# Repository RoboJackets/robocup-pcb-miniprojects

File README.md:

# Robocup 2026 Onboarding Project

## Description

This is the main repo for the 2026 onboarding season of Robojackets Robocup.

## Setup

Have ONE member of your team do this:

```sh
git clone https://github.com/RoboJackets/robocup-pcb-miniprojects
cd robocup-pcb-miniprojects
git checkout -b <your-team-name>
git push -u origin <your-team-name>
```

Now ALL members can:

```sh
git clone https://github.com/RoboJackets/robocup-pcb-miniprojects
cd robocup-pcb-miniprojects
git checkout <your-team-name>
```

This branch is where all work for your project should be done. Do not attempt to modify main, and especially do not try to modify other teams' branches.

## Overview

Your task is to create a daisy-chained sensor suite. Powered by the RP2040, this should be able to take a data packet from an SPI input, add to this packet, and pass it to the next board via SPI. Information for this packet is to be collected from the six distinct I2C devices on the board.

### PCB
Your KiCAD project folder and all other relevant files should be stored in [pcb](/pcb/).

See the [README](/pcb/README.md) for specific information.

### Firmware
Your Pico SDK project folder and all other relevant files should be stored in [firmware](/firmware/).

See the [README](/firmware/README.md) for specific information.

### Documentation

All live documentation (Hardware Reference Manuals, Technical Overviews, etc) should be stored in your team's drive folder which can be found [HERE](https://drive.google.com/drive/folders/1aSuq1g-BM3DlAOSG3E911sSWYeNv8i6k?usp=drive_link).

Start by copying the two template files from the project template folder [HERE](https://drive.google.com/drive/folders/1uaQHIUm1E482NEQLdI7As42oW3_wIS3i?usp=drive_link).

## Additional Notes

Project updates will be added here as needed

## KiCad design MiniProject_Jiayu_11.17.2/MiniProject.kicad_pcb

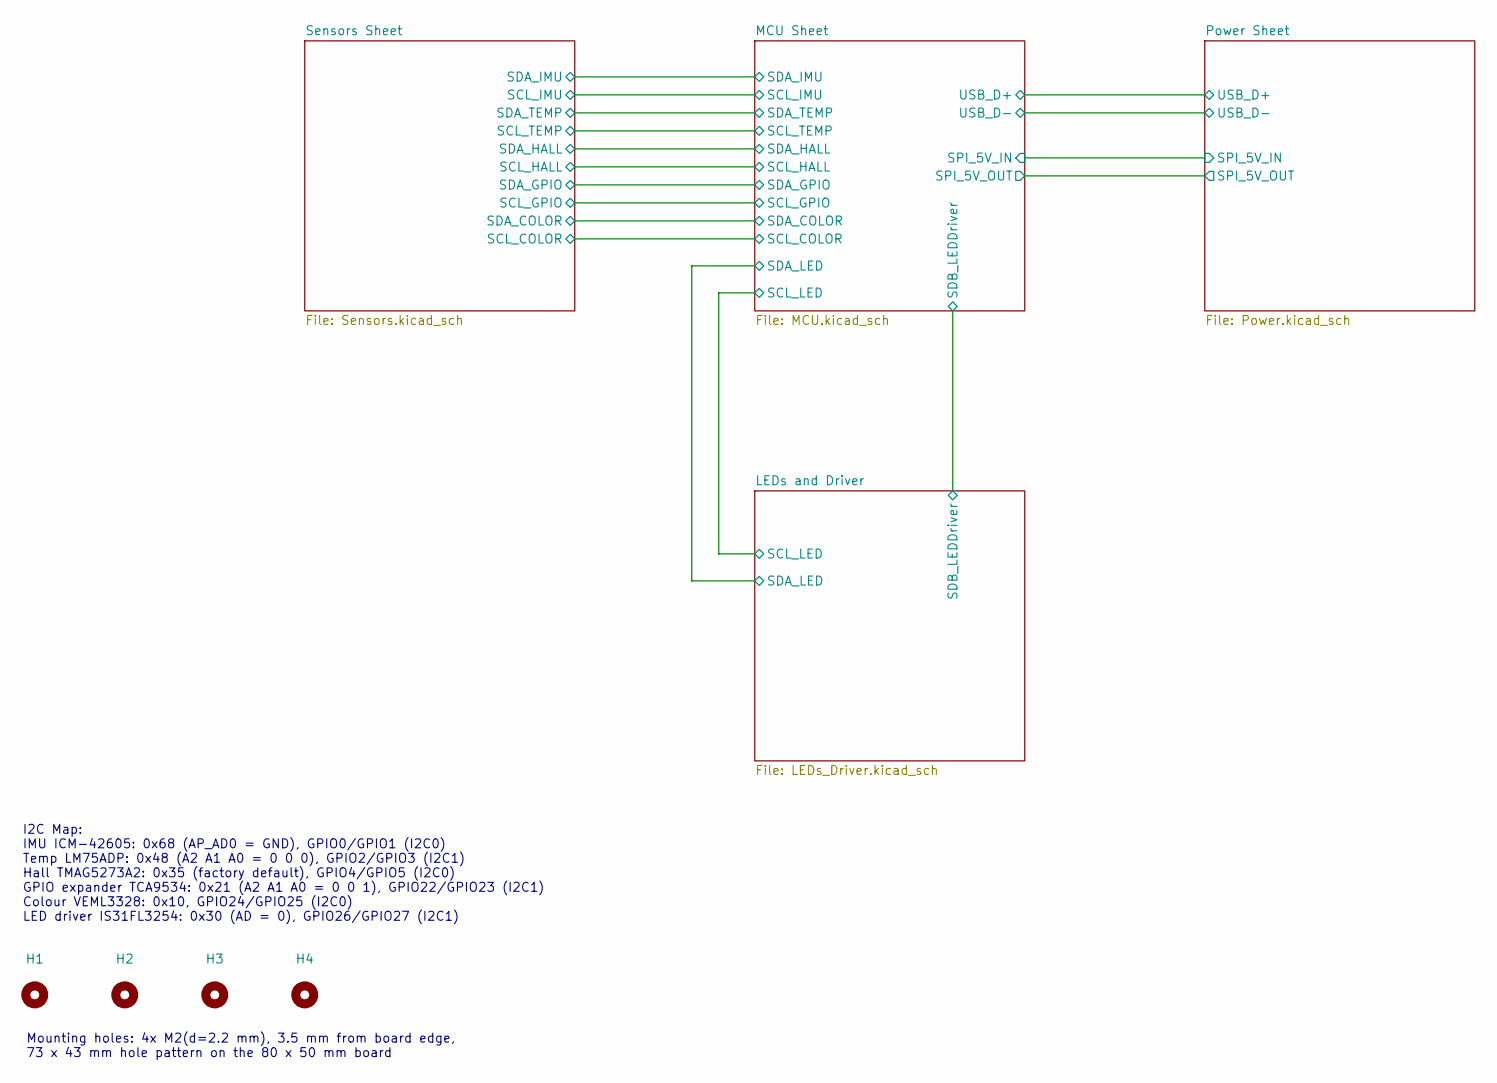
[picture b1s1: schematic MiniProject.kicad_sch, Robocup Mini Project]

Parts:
H1, H2, H3, H4: MountingHole; MountingHole_2.2mm_M2

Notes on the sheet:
I2C Map: IMU ICM-42605: 0x68 (AP_AD0 = GND), GPIO0/GPIO1 (I2C0) Temp LM75ADP: 0x48 (A2 A1 A0 = 0 0 0), GPIO2/GPIO3 (I2C1) Hall TMAG5273A2: 0x35 (factory default), GPIO4/GPIO5 (I2C0) GPIO expander TCA9534: 0x21 (A2 A1 A0 = 0 0 1), GPIO22/GPIO23 (I2C1) Colour VEML3328: 0x10, GPIO24/GPIO25 (I2C0) LED 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
Mounting holes: 4x M2(d=2.2 mm), 3.5 mm from board edge, 73 x 43 mm hole pattern on the 80 x 50 mm board

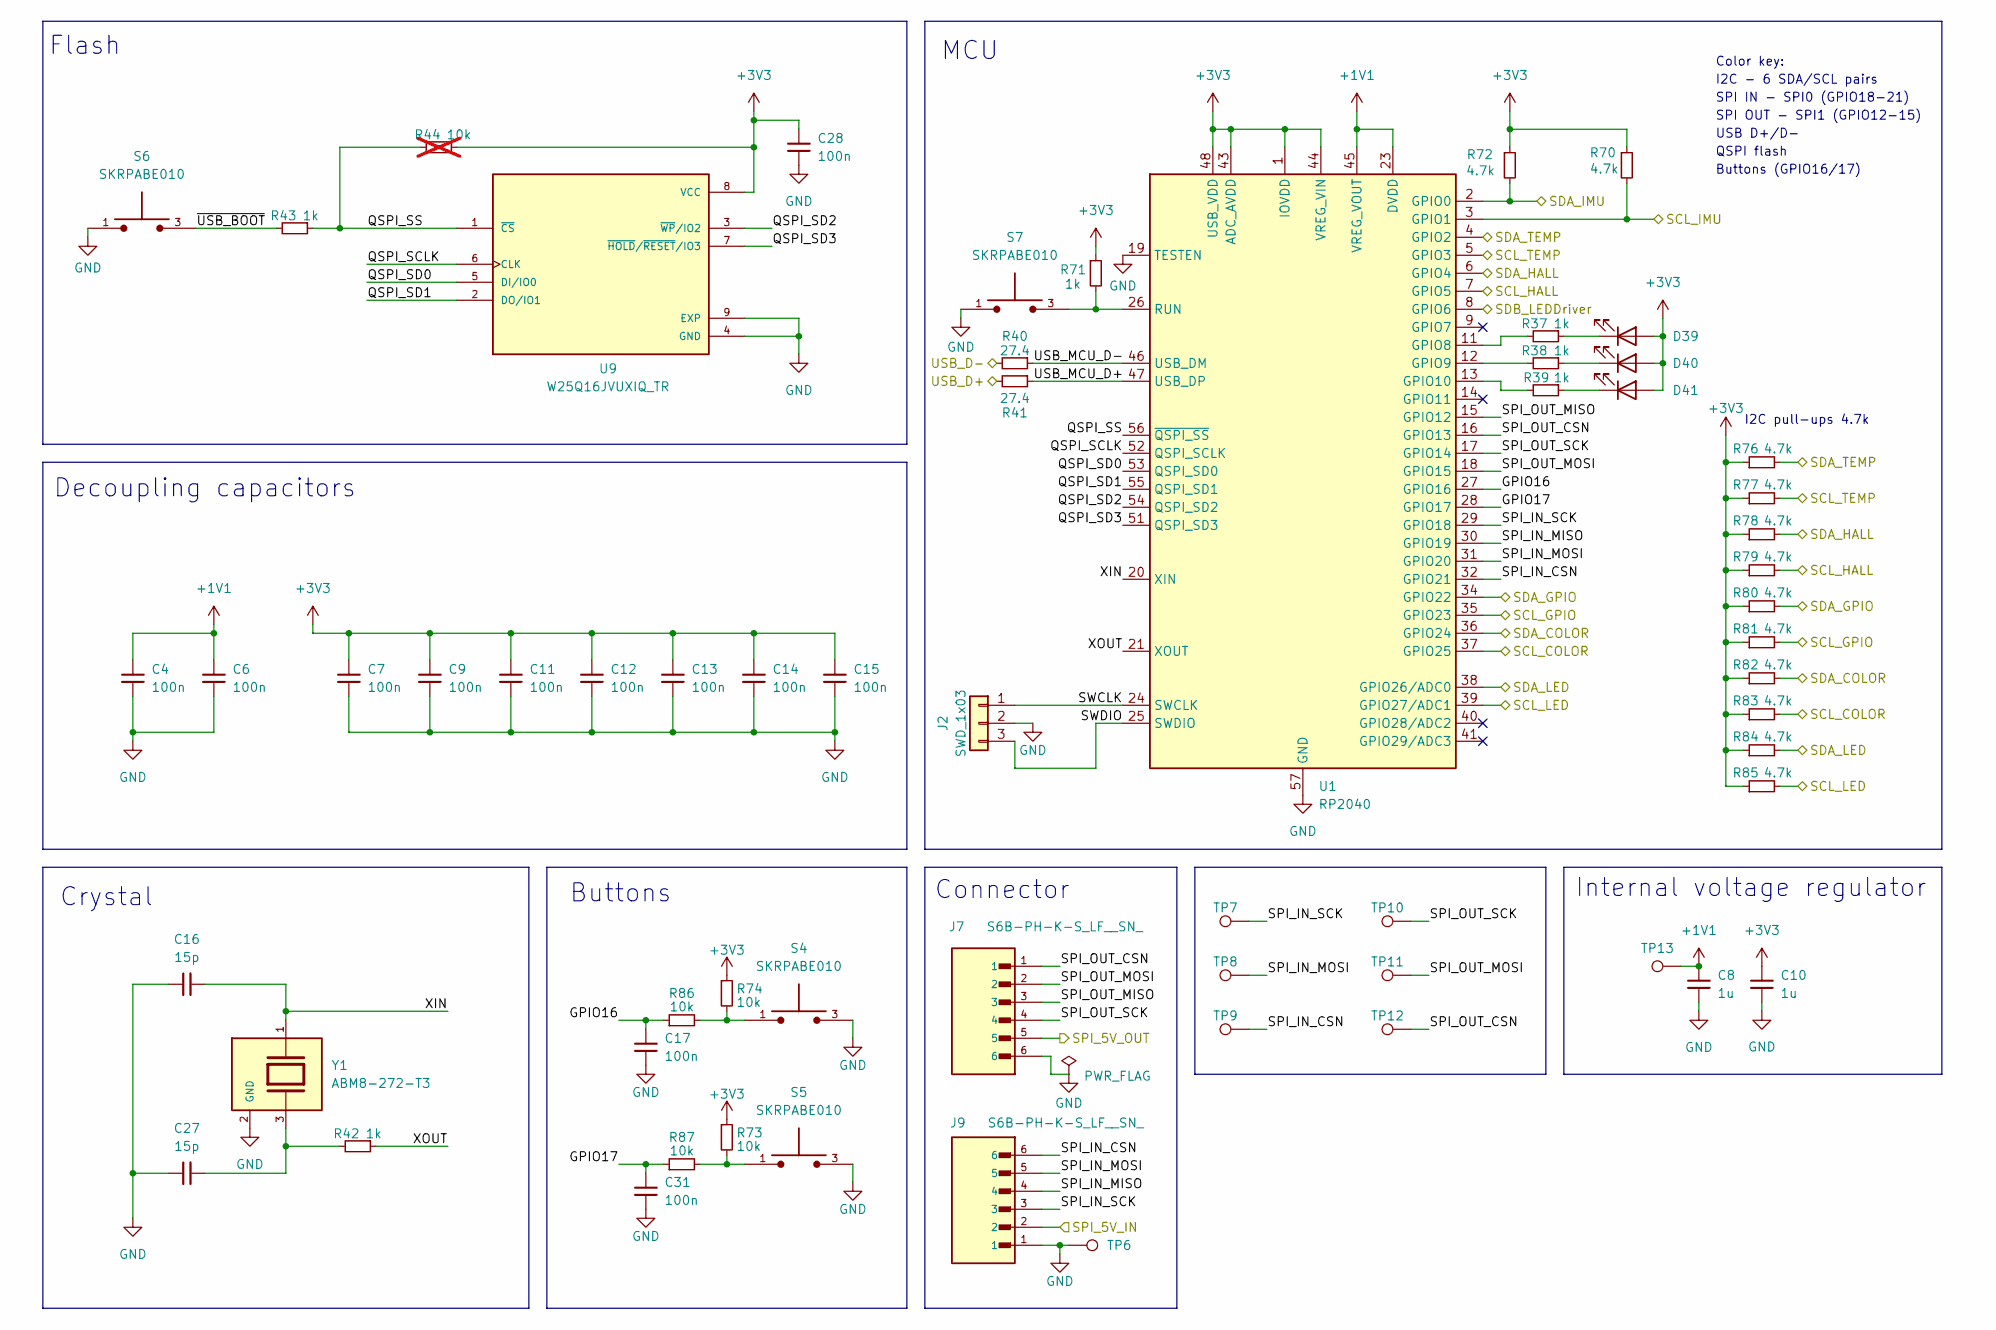
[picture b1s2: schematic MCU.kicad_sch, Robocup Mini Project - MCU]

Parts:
C4, C6, C7, C9, C11, C12, C13, C14, C15, C17, C28, C31: 100n; C_0402_1005Metric; Manufacturer P/N GRM155R71C104KA88J
C8, C10: 1u; C_0402_1005Metric; Manufacturer P/N CL05A105KA5NQNC
C16, C27: 15p; C_0402_1005Metric; Manufacturer P/N CL05C150JB5NNNC
D39, D40, D41: LED; LED_0603_1608Metric; Manufacturer P/N LTST-C191KGKT
J2: SWD_1x03; PinHeader_1x03_P2.54mm_Vertical; Manufacturer P/N TSW-103-07-G-S
J7, J9: S6B-PH-K-S_LF__SN_; JST_S6B-PH-K-S_LF__SN_; Manufacturer P/N S6B-PH-K-S
R37, R38, R39, R42, R43, R71: 1k; R_0402_1005Metric; Manufacturer P/N RC0402FR-071KL
R40, R41: 27.4; R_0402_1005Metric; Manufacturer P/N RC0402FR-0727R4L
R44: 10k; R_0402_1005Metric; Manufacturer P/N RC0402FR-0710KL; not fitted
R70, R72, R76, R77, R78, R79, R80, R81, R82, R83, R84, R85: 4.7k; R_0402_1005Metric; Manufacturer P/N RC0402FR-134K7L
R73, R74, R86, R87: 10k; R_0402_1005Metric; Manufacturer P/N RC0402FR-0710KL
S4, S5, S6, S7: SKRPABE010; SW_SKRPABE010; Manufacturer P/N SKRPABE010
TP6: GND; TestPoint_Pad_D1.0mm
TP7: SPI_IN_SCK; TestPoint_Pad_D1.0mm
TP8: SPI_IN_MOSI; TestPoint_Pad_D1.0mm
TP9: SPI_IN_CSN; TestPoint_Pad_D1.0mm
TP10: SPI_OUT_SCK; TestPoint_Pad_D1.0mm
TP11: SPI_OUT_MOSI; TestPoint_Pad_D1.0mm
TP12: SPI_OUT_CSN; TestPoint_Pad_D1.0mm
TP13: +1V1; TestPoint_Pad_D1.0mm
U1: RP2040; QFN-56-1EP_7x7mm_P0.4mm_EP3.2x3.2mm; Manufacturer P/N SC0914(13)
U9: W25Q16JVUXIQ_TR; Winbond_USON-8-1EP_3x2mm_P0.5mm_EP0.2x1.6mm; Manufacturer P/N W25Q16JVUXIQ TR
Y1: ABM8-272-T3; XTAL_ABM8-272-T3; Manufacturer P/N ABM8-272-T3

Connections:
+1V1: C4.1, C6.1, C8.1, TP13.1, U1.23 (DVDD), U1.45 (VREG_VOUT), U1.50 (DVDD)
+3V3: C7.1, C9.1, C10.1, C11.1, C12.1, C13.1, C14.1, C15.1, C28.1, D39.2 (A), D40.2 (A), D41.2 (A), R44.1, R70.1, R71.1, R72.1, R73.1, R74.1, R76.1, R77.1, R78.1, R79.1, R80.1, R81.1, R82.1, R83.1, R84.1, R85.1, U1.1 (IOVDD), U1.10 (IOVDD), U1.22 (IOVDD), U1.33 (IOVDD), U1.42 (IOVDD), U1.43 (ADC_AVDD), U1.44 (VREG_VIN), U1.48 (USB_VDD), U1.49 (IOVDD), U9.8 (VCC); also elsewhere on the board
/LEDs and Driver/SCL_LED: R85.2, U1.39 (GPIO27/ADC1); also elsewhere on the board
/LEDs and Driver/SDA_LED: R84.2, U1.38 (GPIO26/ADC0); also elsewhere on the board
/LEDs and Driver/SDB_LEDDriver: U1.8 (GPIO6); also elsewhere on the board
/MCU Sheet/GPIO16: C17.1, R86.1, U1.27 (GPIO16)
/MCU Sheet/GPIO17: C31.1, R87.1, U1.28 (GPIO17)
/MCU Sheet/QSPI_SCLK: U1.52 (QSPI_SCLK), U9.6 (CLK)
/MCU Sheet/QSPI_SD0: U1.53 (QSPI_SD0), U9.5 (DI/IO0)
/MCU Sheet/QSPI_SD1: U1.55 (QSPI_SD1), U9.2 (DO/IO1)
/MCU Sheet/QSPI_SD2: U1.54 (QSPI_SD2), U9.3 (~WP/IO2)
/MCU Sheet/QSPI_SD3: U1.51 (QSPI_SD3), U9.7 (~HOLD/~RESET/IO3)
/MCU Sheet/QSPI_SS: R43.1, R44.2, U1.56 (~QSPI_SS), U9.1 (~CS)
/MCU Sheet/SCL_COLOR: R83.2, U1.37 (GPIO25); also elsewhere on the board
/MCU Sheet/SCL_GPIO: R81.2, U1.35 (GPIO23); also elsewhere on the board
/MCU Sheet/SCL_HALL: R79.2, U1.7 (GPIO5); also elsewhere on the board
/MCU Sheet/SCL_IMU: R70.2, U1.3 (GPIO1); also elsewhere on the board
/MCU Sheet/SCL_TEMP: R77.2, U1.5 (GPIO3); also elsewhere on the board
/MCU Sheet/SDA_COLOR: R82.2, U1.36 (GPIO24); also elsewhere on the board
/MCU Sheet/SDA_GPIO: R80.2, U1.34 (GPIO22); also elsewhere on the board
/MCU Sheet/SDA_HALL: R78.2, U1.6 (GPIO4); also elsewhere on the board
/MCU Sheet/SDA_IMU: R72.2, U1.2 (GPIO0); also elsewhere on the board
/MCU Sheet/SDA_TEMP: R76.2, U1.4 (GPIO2); also elsewhere on the board
/MCU Sheet/SPI_5V_IN: J9.2; also elsewhere on the board
/MCU Sheet/SPI_5V_OUT: J7.5; also elsewhere on the board
/MCU Sheet/SPI_IN_CSN: J9.6, TP9.1 (1_1), U1.32 (GPIO21)
/MCU Sheet/SPI_IN_MISO: J9.4, U1.30 (GPIO19)
/MCU Sheet/SPI_IN_MOSI: J9.5, TP8.1 (1_1), U1.31 (GPIO20)
/MCU Sheet/SPI_IN_SCK: J9.3, TP7.1 (1_1), U1.29 (GPIO18)
/MCU Sheet/SPI_OUT_CSN: J7.1, TP12.1 (1_1), U1.16 (GPIO13)
/MCU Sheet/SPI_OUT_MISO: J7.3, U1.15 (GPIO12)
/MCU Sheet/SPI_OUT_MOSI: J7.2, TP11.1 (1_1), U1.18 (GPIO15)
/MCU Sheet/SPI_OUT_SCK: J7.4, TP10.1 (1_1), U1.17 (GPIO14)
/MCU Sheet/SWCLK: J2.1, U1.24 (SWCLK)
/MCU Sheet/SWDIO: J2.3, U1.25 (SWDIO)
/MCU Sheet/USB_D+: R41.2; also elsewhere on the board
/MCU Sheet/USB_D-: R40.2; also elsewhere on the board
/MCU Sheet/USB_MCU_D+: R41.1, U1.47 (USB_DP)
/MCU Sheet/USB_MCU_D-: R40.1, U1.46 (USB_DM)
/MCU Sheet/XIN: C16.2, U1.20 (XIN), Y1.1
/MCU Sheet/XOUT: R42.1, U1.21 (XOUT)
/MCU Sheet/~USB_BOOT: R43.2, S6.3, S6.4
GND: C4.2, C6.2, C7.2, C8.2, C9.2, C10.2, C11.2, C12.2, C13.2, C14.2, C15.2, C16.1, C17.2, C27.1, C28.2, C31.2, J2.2, J7.6, J9.1, S4.3, S4.4, S5.3, S5.4, S6.1, S6.2, S7.1, S7.2, TP6.1 (1_1), U1.19 (TESTEN), U1.57 (GND), U9.4 (GND), U9.9 (EXP), Y1.2 (GND), Y1.4 (GND); also elsewhere on the board
unnamed: C27.2, R42.2, Y1.3
unnamed: D39.1 (K), R37.1
unnamed: D40.1 (K), R38.1
unnamed: D41.1 (K), R39.1
unnamed: R73.2, R87.2, S5.1, S5.2
unnamed: R74.2, R86.2, S4.1, S4.2
unnamed: R37.2, U1.11 (GPIO8)
unnamed: R38.2, U1.12 (GPIO9)
unnamed: R39.2, U1.13 (GPIO10)
unnamed: R71.2, S7.3, S7.4, U1.26 (RUN)

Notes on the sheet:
SPI OUT - SPI1 (GPIO12-15)
I2C - 6 SDA/SCL pairs
Connector
SPI IN - SPI0 (GPIO18-21)
I2C pull-ups 4.7k
Decoupling capacitors
QSPI flash
Flash
Internal voltage regulator
Buttons
Color key:
USB D+/D-
Crystal
Buttons (GPIO16/17)
MCU

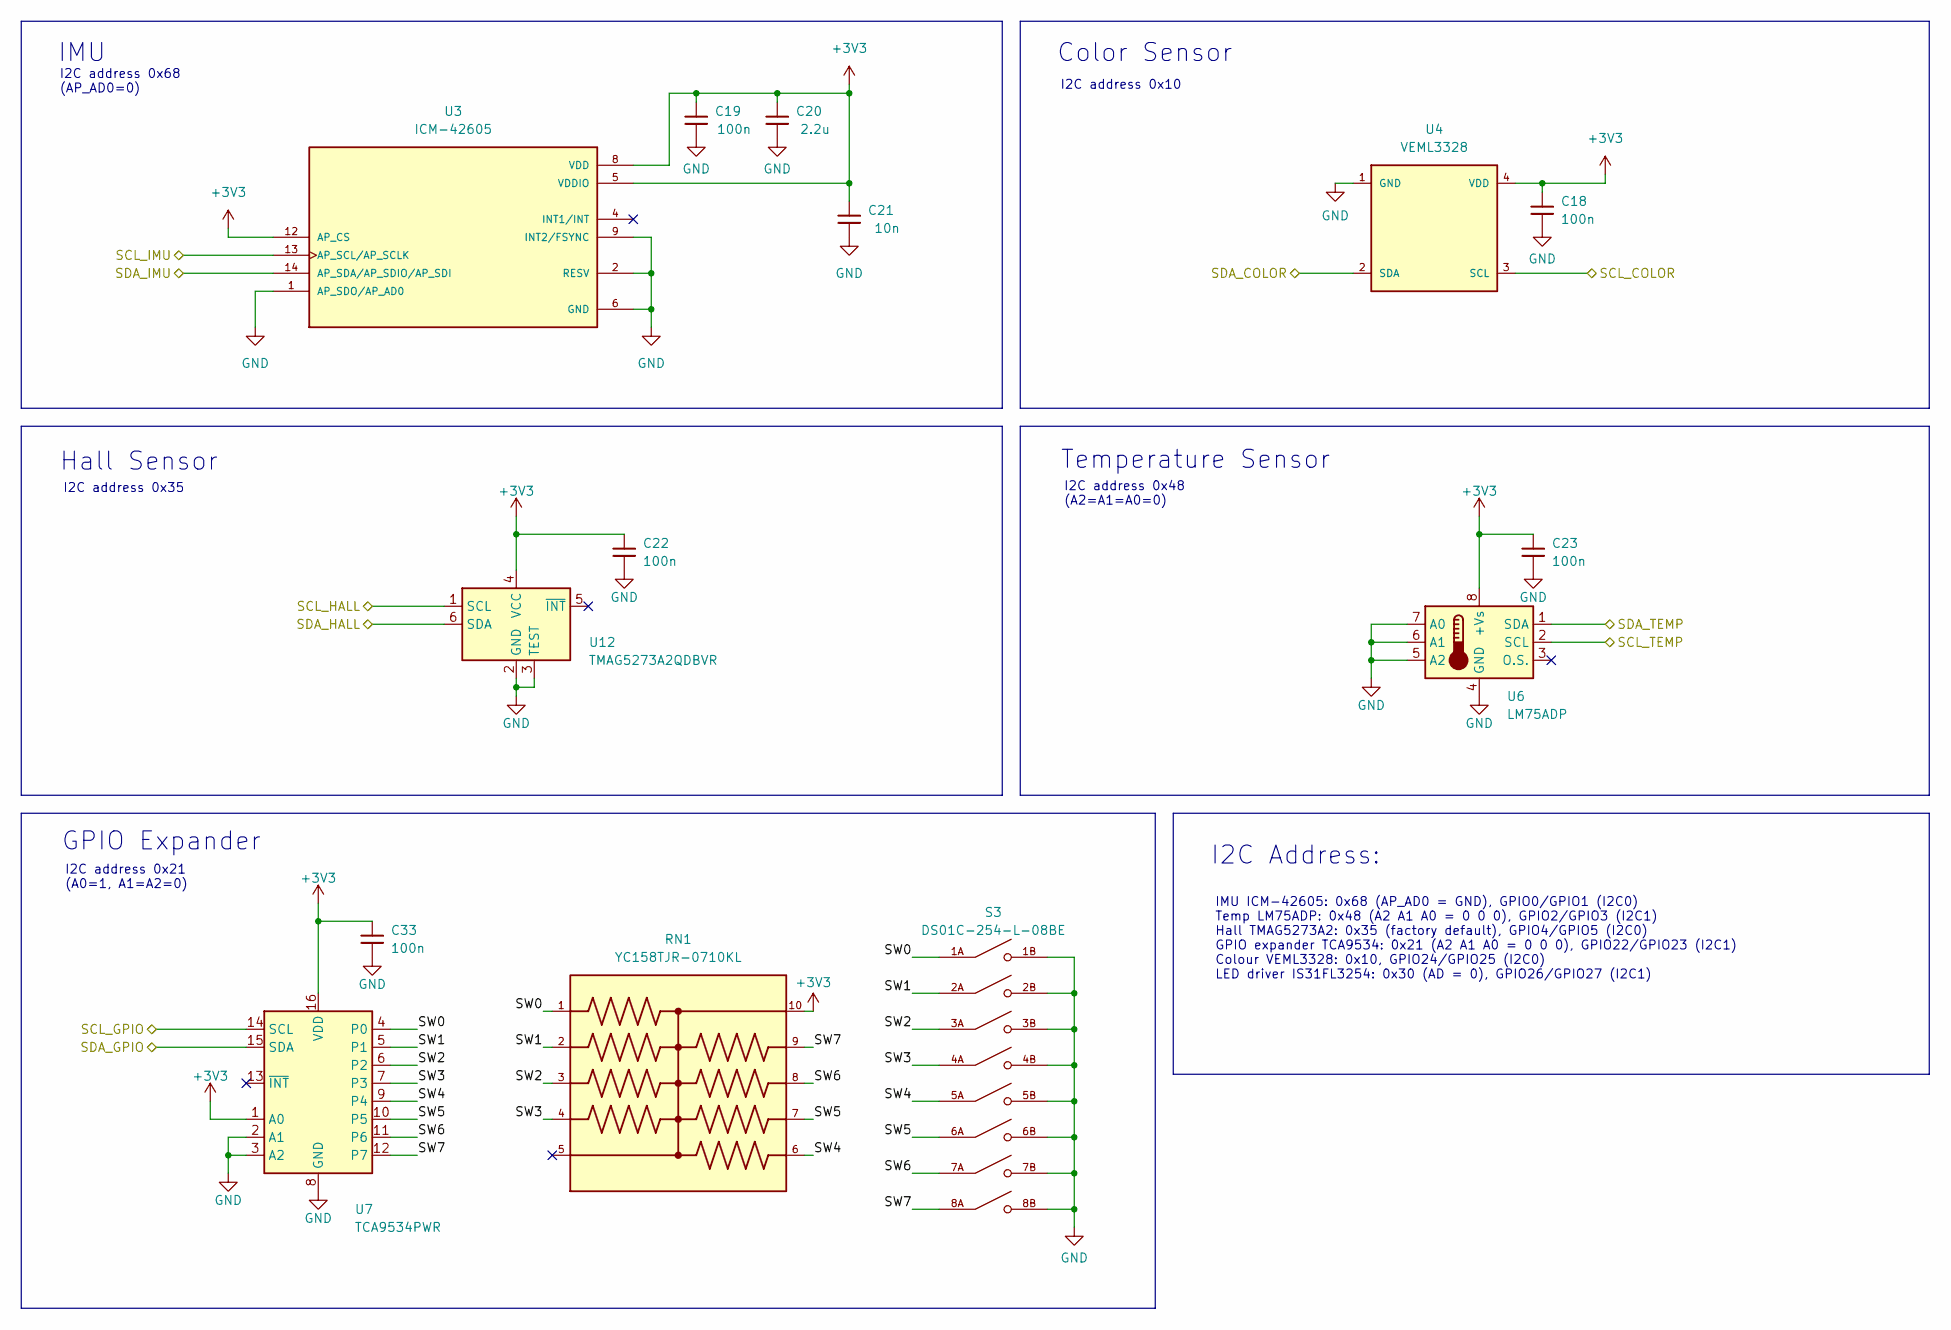
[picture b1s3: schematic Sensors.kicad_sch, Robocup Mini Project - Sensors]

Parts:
C18, C19, C22, C23, C33: 100n; C_0402_1005Metric; Manufacturer P/N GRM155R71C104KA88J
C20: 2.2u; C_0402_1005Metric; Manufacturer P/N LMK105BJ225KV-F
C21: 10n; C_0402_1005Metric; Manufacturer P/N CL05B103KB5NNNC
RN1: YC158TJR-0710KL; RESCAXE64P320X160X70-10N; Manufacturer P/N YC158TJR-0710KL
S3: DS01C-254-L-08BE; SW_DS01C-254-L-08BE; Manufacturer P/N DS01C-254-L-08BE
U3: ICM-42605; XDCR_ICM-42605; Manufacturer P/N ICM-42605
U4: VEML3328; Manufacturer P/N VEML3328
U6: LM75ADP; TSSOP-8_3x3mm_P0.65mm; Manufacturer P/N LM75ADP,118
U7: TCA9534PWR; SOP65P640X120-16N; Manufacturer P/N TCA9534PWR
U12: TMAG5273A2QDBVR; SOT95P280X140-6N; Manufacturer P/N TMAG5273A2QDBVR

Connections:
+3V3: C18.1, C19.1, C20.1, C21.1, C22.1, C23.1, C33.1, RN1.10, U3.5 (VDDIO), U3.8 (VDD), U3.12 (AP_CS), U4.4 (VDD), U6.8 (+Vs), U7.1 (A0), U7.16 (VCC), U12.4 (VCC); also elsewhere on the board
/MCU Sheet/SCL_COLOR: U4.3 (SCL); also elsewhere on the board
/MCU Sheet/SCL_GPIO: U7.14 (SCL); also elsewhere on the board
/MCU Sheet/SCL_HALL: U12.1 (SCL); also elsewhere on the board
/MCU Sheet/SCL_IMU: U3.13 (AP_SCL/AP_SCLK); also elsewhere on the board
/MCU Sheet/SCL_TEMP: U6.2 (SCL); also elsewhere on the board
/MCU Sheet/SDA_COLOR: U4.2 (SDA); also elsewhere on the board
/MCU Sheet/SDA_GPIO: U7.15 (SDA); also elsewhere on the board
/MCU Sheet/SDA_HALL: U12.6 (SDA); also elsewhere on the board
/MCU Sheet/SDA_IMU: U3.14 (AP_SDA/AP_SDIO/AP_SDI); also elsewhere on the board
/MCU Sheet/SDA_TEMP: U6.1 (SDA); also elsewhere on the board
/Sensors Sheet/SW0: RN1.1, S3.1A, U7.4 (P0)
/Sensors Sheet/SW1: RN1.2, S3.2A, U7.5 (P1)
/Sensors Sheet/SW2: RN1.3, S3.3A, U7.6 (P2)
/Sensors Sheet/SW3: RN1.4, S3.4A, U7.7 (P3)
/Sensors Sheet/SW4: RN1.6, S3.5A, U7.9 (P4)
/Sensors Sheet/SW5: RN1.7, S3.6A, U7.10 (P5)
/Sensors Sheet/SW6: RN1.8, S3.7A, U7.11 (P6)
/Sensors Sheet/SW7: RN1.9, S3.8A, U7.12 (P7)
GND: C18.2, C19.2, C20.2, C21.2, C22.2, C23.2, C33.2, S3.1B, S3.2B, S3.3B, S3.4B, S3.5B, S3.6B, S3.7B, S3.8B, U3.1 (AP_SDO/AP_AD0), U3.2 (RESV), U3.3 (RESV), U3.6 (GND), U3.7 (RESV), U3.9 (INT2/FSYNC), U3.10 (RESV), U3.11 (RESV), U4.1 (GND), U6.4 (GND), U6.5 (A2), U6.6 (A1), U6.7 (A0), U7.2 (A1), U7.3 (A2), U7.8 (GND), U12.2 (GND), U12.3 (TEST); also elsewhere on the board

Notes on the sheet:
Temperature Sensor
I2C Address:
IMU ICM-42605: 0x68 (AP_AD0 = GND), GPIO0/GPIO1 (I2C0) Temp LM75ADP: 0x48 (A2 A1 A0 = 0 0 0), GPIO2/GPIO3 (I2C1) Hall TMAG5273A2: 0x35 (factory default), GPIO4/GPIO5 (I2C0) GPIO expander TCA9534: 0x21 (A2 A1 A0 = 0 0 0), GPIO22/GPIO23 (I2C1) Colour VEML3328: 0x10, GPIO24/GPIO25 (I2C0) LED driver IS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
GPIO Expander
I2C address 0x21 (A0=1, A1=A2=0)
Color Sensor
I2C address 0x68 (AP_AD0=0)
I2C address 0x35
Hall Sensor
IMU
I2C address 0x10
I2C address 0x48 (A2=A1=A0=0)

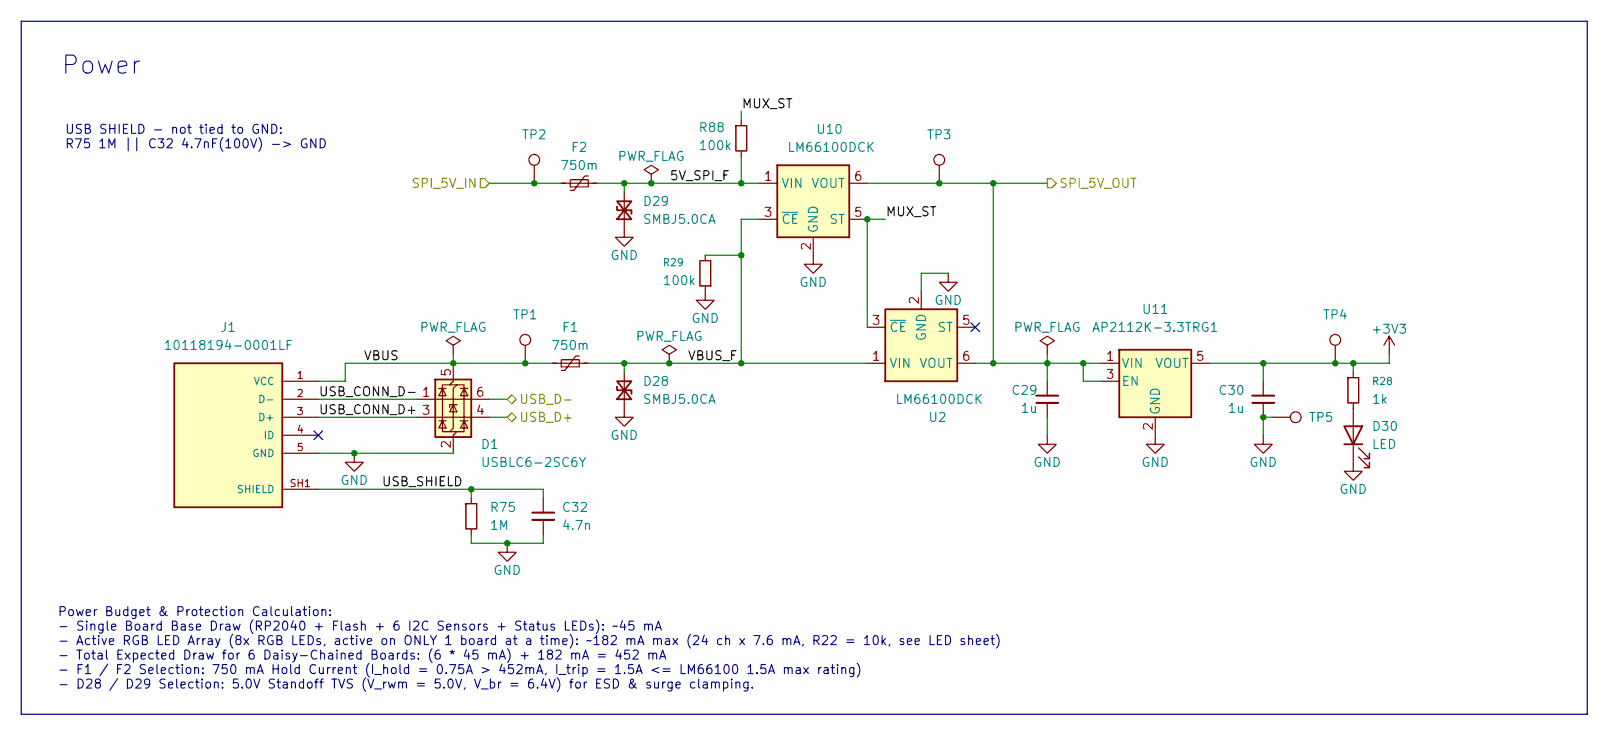
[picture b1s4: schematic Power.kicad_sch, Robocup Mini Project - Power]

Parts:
C29, C30: 1u; C_0402_1005Metric; Manufacturer P/N CL05A105KA5NQNC
C32: 4.7n; C_0603_1608Metric; Manufacturer P/N C1608X7R2A472K080AA
D1: USBLC6-2SC6Y; SOT95P280X145-6N; Manufacturer P/N USBLC6-2SC6Y
D28, D29: SMBJ5.0CA; D_SMB; Manufacturer P/N SMBJ5.0CA
D30: LED; LED_0402_1005Metric; Manufacturer P/N LTST-C281KRKT
F1, F2: 750m; Fuse_0805_2012Metric; Manufacturer P/N MF-PSMF075X-2
J1: 10118194-0001LF; AMPHENOL_10118194-0001LF; Manufacturer P/N 10118194-0001LF
R28: 1k; R_0402_1005Metric; Manufacturer P/N RC0402FR-071KL
R29, R88: 100k; R_0402_1005Metric; Manufacturer P/N RC0402FR-07100KL
R75: 1M; R_0402_1005Metric; Manufacturer P/N RC0402FR-071ML
TP1: VBUS; TestPoint_Pad_D1.0mm
TP2: SPI_5V_IN; TestPoint_Pad_D1.0mm
TP3: SPI_5V_OUT; TestPoint_Pad_D1.0mm
TP4: +3V3; TestPoint_Pad_D1.0mm
TP5: GND; TestPoint_Pad_D1.0mm
U2, U10: LM66100DCK; SOT-363_SC-70-6; Manufacturer P/N LM66100DCKR
U11: AP2112K-3.3TRG1; SOT95P285X140-5N; Manufacturer P/N AP2112K-3.3TRG1

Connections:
+3V3: C30.1, R28.1, TP4.1 (1_1), U11.5 (VOUT); also elsewhere on the board
/MCU Sheet/SPI_5V_IN: F2.1, TP2.1 (1_1); also elsewhere on the board
/MCU Sheet/SPI_5V_OUT: C29.1, TP3.1 (1_1), U2.6 (VOUT), U10.6 (VOUT), U11.1 (VIN), U11.3 (EN); also elsewhere on the board
/MCU Sheet/USB_D+: D1.4 (I/O2_2); also elsewhere on the board
/MCU Sheet/USB_D-: D1.6 (I/O1_2); also elsewhere on the board
/Power Sheet/5V_SPI_F: D29.2 (A2), F2.2, R88.2, U10.1 (VIN)
/Power Sheet/MUX_ST: R88.1, U2.3 (~CE), U10.5 (ST)
/Power Sheet/USB_CONN_D+: D1.3 (I/O2_1), J1.3 (D+)
/Power Sheet/USB_CONN_D-: D1.1 (I/O1_1), J1.2 (D-)
/Power Sheet/USB_SHIELD: C32.1, J1.SH1 (SHIELD), J1.SH2 (SHIELD), J1.SH3 (SHIELD), J1.SH4 (SHIELD), J1.SH5 (SHIELD), J1.SH6 (SHIELD), R75.1
/Power Sheet/VBUS: D1.5 (VBUS), F1.1, J1.1 (VCC), TP1.1 (1_1)
/Power Sheet/VBUS_F: D28.2 (A2), F1.2, R29.2, U2.1 (VIN), U10.3 (~CE)
GND: C29.2, C30.2, C32.2, D1.2 (GND), D28.1 (A1), D29.1 (A1), D30.1 (K), J1.5 (GND), R29.1, R75.2, TP5.1 (1_1), U2.2 (GND), U10.2 (GND), U11.2 (GND); also elsewhere on the board
unnamed: D30.2 (A), R28.2

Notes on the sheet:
Power
USB SHIELD - not tied to GND: R75 1M || C32 4.7nF(100V) -> GND
Power Budget & Protection Calculation: - Single Board Base Draw (RP2040 + Flash + 6 I2C Sensors + Status LEDs): ~45 mA - Active RGB LED Array (8x RGB LEDs, active on ONLY 1 board at a time): ~182 mA max (24 ch x 7.6 mA, R22 = 10k, see LED sheet) - Total Expected Draw for 6 Daisy-Chained Boards: (6 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

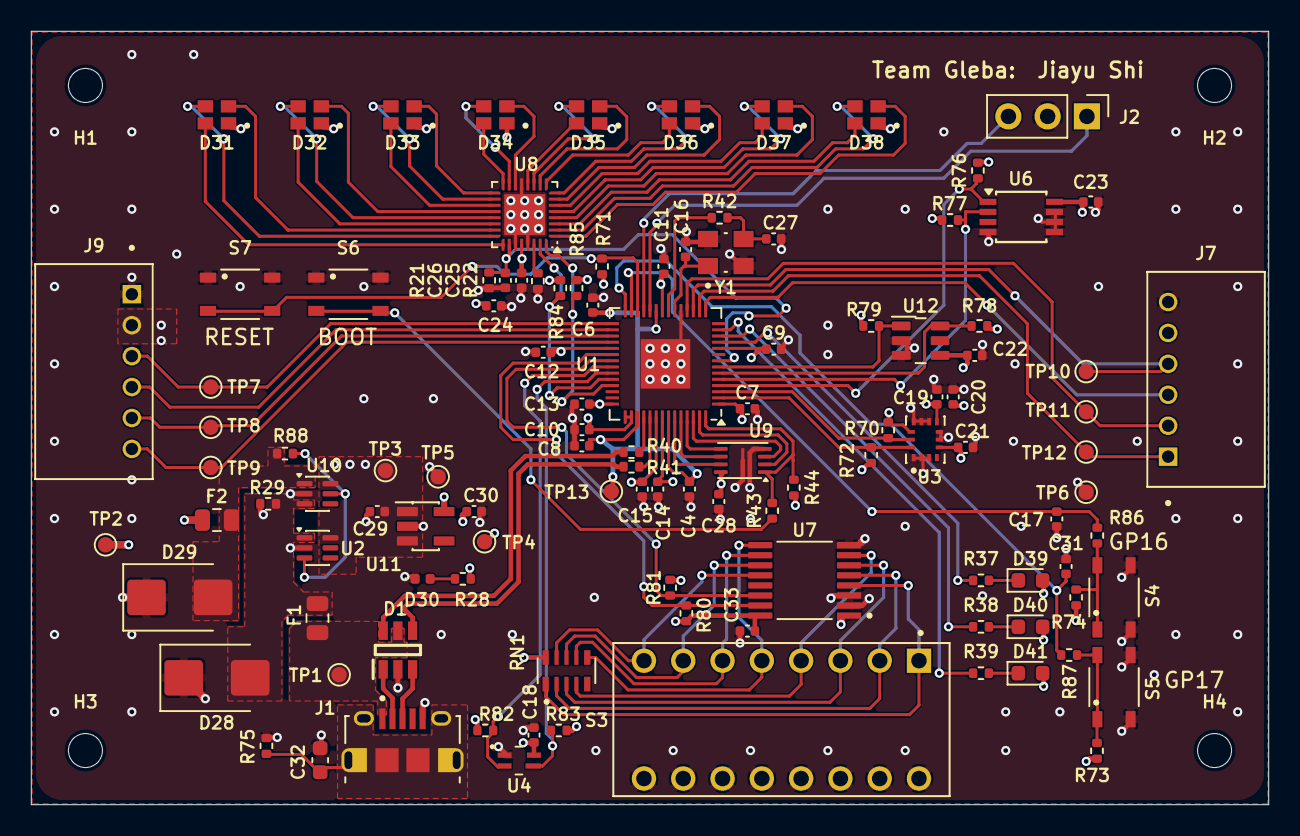
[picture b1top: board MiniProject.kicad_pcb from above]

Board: 4 copper layers, 80.0 x 50.0 mm, 117 parts (1 on the bottom side), 94 nets.

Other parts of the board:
C24: 1u; C_0402_1005Metric
C25, C26: 100n; C_0402_1005Metric
D31, D32, D33, D34, D35, D36, D37, D38: CLMVC-FKA-CL1D1L71BB7C3C3; LED_CLMVC-FKA-CL1D1L71BB7C3C3
LOGO1: RoboJackets_Logo_3x
R21: 100k; R_0402_1005Metric
R22: 10k; R_0402_1005Metric
U8: IS31FL3254-QFLS4-TR; QFN-32-1EP_4x4mm_P0.4mm_EP2.65x2.65mm

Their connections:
+3V3: C24.1, C25.1, D31.1, D32.1, D33.1, D34.1, D35.1, D36.1, D37.1, D38.1, U8.28 (VCC); also elsewhere on the board
/LEDs and Driver/OUT1_R1: D38.4, U8.1 (OUT1_R1)
/LEDs and Driver/OUT2_G1: D38.3, U8.2 (OUT2_G1)
/LEDs and Driver/OUT3_B1: D38.2, U8.3 (OUT3_B1)
/LEDs and Driver/OUT4_R2: D37.4, U8.4 (OUT4_R2)
/LEDs and Driver/OUT5_G2: D37.3, U8.5 (OUT5_G2)
/LEDs and Driver/OUT6_B2: D37.2, U8.6 (OUT6_B2)
/LEDs and Driver/OUT7_R3: D36.4, U8.7 (OUT7_R3)
/LEDs and Driver/OUT8_G3: D36.3, U8.8 (OUT8_G3)
/LEDs and Driver/OUT9_B3: D36.2, U8.9 (OUT9_B3)
/LEDs and Driver/OUT10_R4: D35.4, U8.10 (OUT10_R4)
/LEDs and Driver/OUT11_G4: D35.3, U8.11 (OUT11_G4)
/LEDs and Driver/OUT12_B4: D35.2, U8.12 (OUT12_B4)
/LEDs and Driver/OUT13_R5: D34.4, U8.14 (OUT13_R5)
/LEDs and Driver/OUT14_G5: D34.3, U8.15 (OUT14_G5)
/LEDs and Driver/OUT15_B5: D34.2, U8.16 (OUT15_B5)
/LEDs and Driver/OUT16_R6: D33.4, U8.17 (OUT16_R6)
/LEDs and Driver/OUT17_G6: D33.3, U8.18 (OUT17_G6)
/LEDs and Driver/OUT18_B6: D33.2, U8.19 (OUT18_B6)
/LEDs and Driver/OUT19_R7: D32.4, U8.20 (OUT19_R7)
/LEDs and Driver/OUT20_G7: D32.3, U8.21 (OUT20_G7)
/LEDs and Driver/OUT21_B7: D32.2, U8.22 (OUT21_B7)
/LEDs and Driver/OUT22_R8: D31.4, U8.23 (OUT22_R8)
/LEDs and Driver/OUT23_G8: D31.3, U8.24 (OUT23_G8)
/LEDs and Driver/OUT24_B8: D31.2, U8.25 (OUT24_B8)
/LEDs and Driver/SCL_LED: U8.32 (SCL); also elsewhere on the board
/LEDs and Driver/SDA_LED: U8.31 (SDA); also elsewhere on the board
/LEDs and Driver/SDB_LEDDriver: C26.1, R21.2, U8.26 (SDB); also elsewhere on the board
GND: C24.2, C25.2, C26.2, R21.1, R22.1, U8.13 (GND), U8.27 (AD), U8.29 (GND), U8.33 (EP); also elsewhere on the board
unnamed: R22.2, U8.30 (ISET)

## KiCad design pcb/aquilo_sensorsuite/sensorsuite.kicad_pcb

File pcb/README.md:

# Daisy-Chained Sensor Suite PCB

## Overview

You will be planning, designing, and laying out the PCB for a daisy-chainable sensor suite. The core features of this board will be a RP2040 MCU, Micro USB programming/power input, SPI I/O, and six I2C peripherals.

## Requirements

Additional design specifications can be found in the Hardware Reference Manual (HRM).

1. Documentation
    - While most major parts are pre-selected for you, the documentation for these has not been. You will need to finish filling out the missing sections in the HRM for each component.
    - If you add any new components with a major impact on the final product, make sure to include them as well
    - Overall, keep your HRM as up to date as possible with as much important information as possible so your firmware team can progress along side you
2. PCB
    - Must be manufacturable
        - See JLCPCB capabilities [HERE](https://jlcpcb.com/capabilities/pcb-capabilities)
        - *Hint hint nudge nudge an option for board settings is to import from another board, and Robocup might have boards with similar design requirements [HERE](https://github.com/RoboJackets/robocup-pcb)*
    - Four layers max
        - Going below four is not recommended
    - Size
        - 80mm X 50mm
    - Must pass DRC
        - Will be checked with the Robocup standard DRC suite (if you followed the hint this likely will not be an issue)
    - Must consider signal integrity
    - Must have a legible and correct silkscreen
        - Labels by components or otherwise noted
        - Location for serial number
        - Identifier for all those who worked on it
        - Bonus points for fitting the Robojackets logo
    - Must meet overall required specifications
    - Must have 4 mounting holes (M2)
3. Schematic
    - Must utilize a hierarchy of sheets
        - Do not even ask for a design review of a schematic all crammed on one sheet it is not feasible for the expected complexity
        - Also do not excessively break into sub-sheets, consider what is seperate/repeatable enough to place in a sub-sheet.
    - Notate important characteristics in the schematic
        - General comments
        - Section functionality
        - Placement location requirements
        - Component relevant information
        - The less you have to check the HRM the better
    - Must fill out all sheet information in the right corner
        - Include an additional note for designer name
    - Symbol fields
        - You must fill out all default fields of major components. Non-specialized passives just need footprint and value
        - You must add the field "Vendor P/N" to every specific component with the value set to the Digikey part number
    - When you need to make/import new symbols/footprints/3D models, add them to a new custom library called "local" and store their files if needed in [lib](./lib/)
    - Maintain neatness and readability throughout the schematic
        - General signal flow should go left to right
        - Favor wire net labels over long track wires/grouped outputs
        - Group components by relation/usage
4. Power
    - Power must be able to come from both the USB port and the previous board's SPI line and they must never touch
        - See power MUXing
    - Your power must have appropriate protection for issues such as reverse voltage, ESD, shorts, etc.
    - Your total power draw, and expected power draw for six connected boards must be noted in your schematic and reflected in your protection circuits 
        - Note only one board with an LED array will be active at once
    - There must be some indication that power is connected to the board
5. I2C Devices
    - Must have all six I2C devices and their complementary circuits
        1. IMU
        2. Temperature Sensor
        3. Hall Effect Sensor
        4. GPIO expander
            - Connected to 8 switch DIP switch
            - Resistor network pullup
        5. Color Sensor
        6. LED PWM Controller
            - 8 RGB LEDs
    - Each device must have have different I2C lines
        - However they can share I2C buses
    - Do not use interrupt lines
        - Leave safely disconnected per design requirements
6. Interface
    - Must have at least two general purpose buttons
    - Must have at least three general purpose LEDs
    - Must have test points for all important voltage/signal sources
7. Overall
    - All parts must be in-stock at Digikey at time of completion
        - Yes, if stock runs out during the duration of the project this is still on you to catch
        - You can disregard this rule for parts from the Part Selection specification

## Specifications

### Part Selection

These parts have already been selected for you

- MCU: RP2040
    - 2648-SC0914(13)TR-ND
- 2MB Flash: W25Q16JVUXIQ TR
    - 256-W25Q16JVUXIQTR-ND
- 12MHz Crystal: ABM8-272-T3
    - 535-ABM8-272-T3TR-ND
- IMU: ICM-42605
    - 1428-1152-2-ND
- Color Sensor: VEML3328
    - 751-VEML3328TR-ND
- Hall Effect Sensor: TMAG5273A2QDBVR
    - 296-TMAG5273A2QDBVRTR-ND
- Temperature Sensor: LM75ADP
    - 568-4227-1-ND
- GPIO Expander: TCA9534PWR
    - 296-40574-2-ND
- DIP Switch: DS01C-254-L-08BE
    - 2223-DS01C-254-L-08BE-ND
- 10kOhm Resistor Network: YC158TJR-0710KL
    - 13-YC158TJR-0710KLTR-ND
- LED Controller: IS31FL3254-QFLS4-TR
    - 2521-IS31FL3254-QFLS4-TR-ND
- RGB LEDs: CLMVC-FKA-CL1D1L71BB7C3C3
    - CLMVC-FKA-CL1D1L71BB7C3C3TR-ND
- Micro USB Connector: 10118194-0001LF
    - 609-4618-2-ND
- SPI Connector: S6B-PH-K-S
    - 455-1723-ND
- 3.3V Linear Regulator: AP2112K-3.3
    - AP2112K-3.3TRG1DITR-ND
- OR Controller: LM66100DCKR
    - 296-53541-2-ND
- General Purpose LEDs (3)
    - 0603 LEDs
- General Purpose Buttons (2): SKRPABE010
    - 4809-SKRPABE010TR-ND

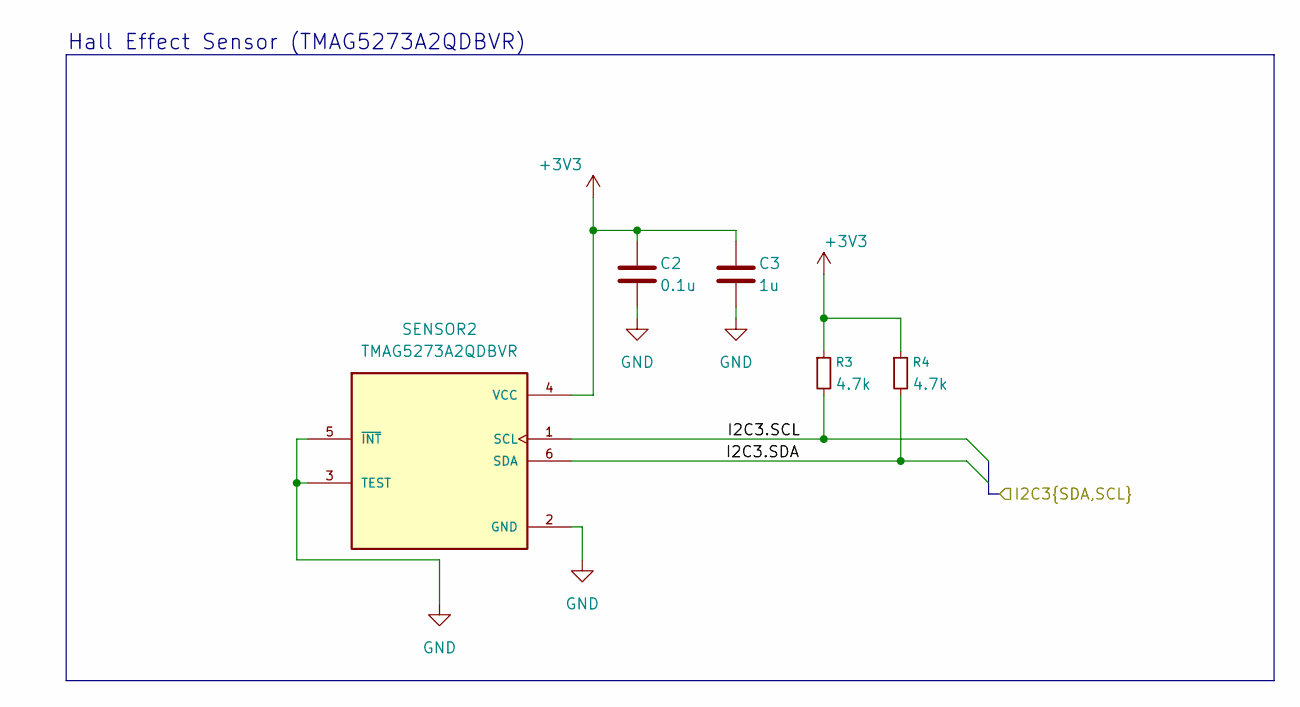
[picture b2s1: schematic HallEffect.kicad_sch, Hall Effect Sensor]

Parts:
C2: 0.1u; C_0402_1005Metric; Manufacturer P/N 0402B104K160HI
C3: 1u; C_0402_1005Metric; Manufacturer P/N 0402W105M6R3HI
R3, R4: 4.7k; R_0402_1005Metric; Manufacturer P/N RK73H1ETTP4701F
SENSOR2: TMAG5273A2QDBVR; SOT95P280X140-6N; Manufacturer P/N TMAG5273A2QDBVR

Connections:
+3V3: C2.1, C3.1, R3.1, R4.1, SENSOR2.4 (VCC); also elsewhere on the board
/Hall Effect Sensor/I2C3.SCL: R3.2, SENSOR2.1 (SCL); also elsewhere on the board
/Hall Effect Sensor/I2C3.SDA: R4.2, SENSOR2.6 (SDA); also elsewhere on the board
GND: C2.2, C3.2, SENSOR2.2 (GND), SENSOR2.3 (TEST), SENSOR2.5 (~INT); also elsewhere on the board

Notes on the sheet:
Hall Effect Sensor (TMAG5273A2QDBVR)

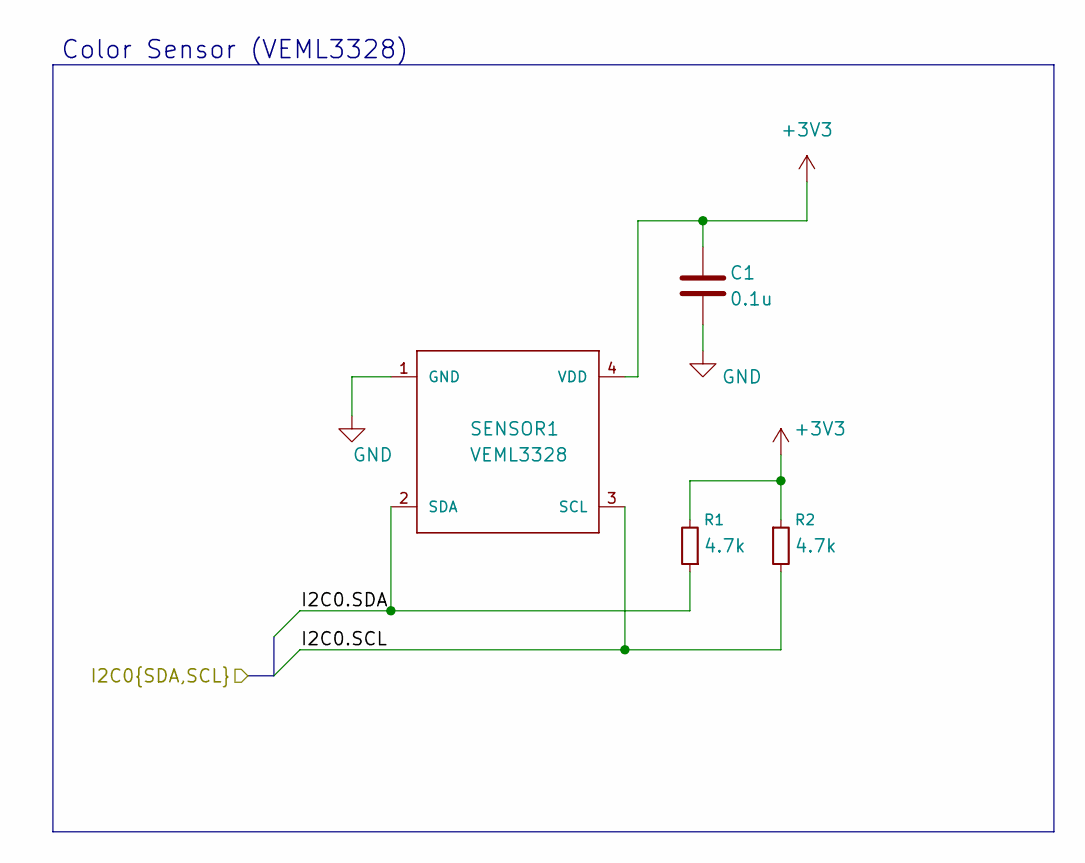
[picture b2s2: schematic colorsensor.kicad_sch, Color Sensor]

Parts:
C1: 0.1u; C_0402_1005Metric; Manufacturer P/N 0402B104K160HI
R1, R2: 4.7k; R_0402_1005Metric; Manufacturer P/N RK73H1ETTP4701F
SENSOR1: VEML3328; Manufacturer P/N VEML3328

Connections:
+3V3: C1.1, R1.2, R2.1, SENSOR1.4 (VDD); also elsewhere on the board
/Color Sensor/I2C0.SCL: R2.2, SENSOR1.3 (SCL); also elsewhere on the board
/Color Sensor/I2C0.SDA: R1.1, SENSOR1.2 (SDA); also elsewhere on the board
GND: C1.2, SENSOR1.1 (GND); also elsewhere on the board

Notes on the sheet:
Color Sensor (VEML3328)
